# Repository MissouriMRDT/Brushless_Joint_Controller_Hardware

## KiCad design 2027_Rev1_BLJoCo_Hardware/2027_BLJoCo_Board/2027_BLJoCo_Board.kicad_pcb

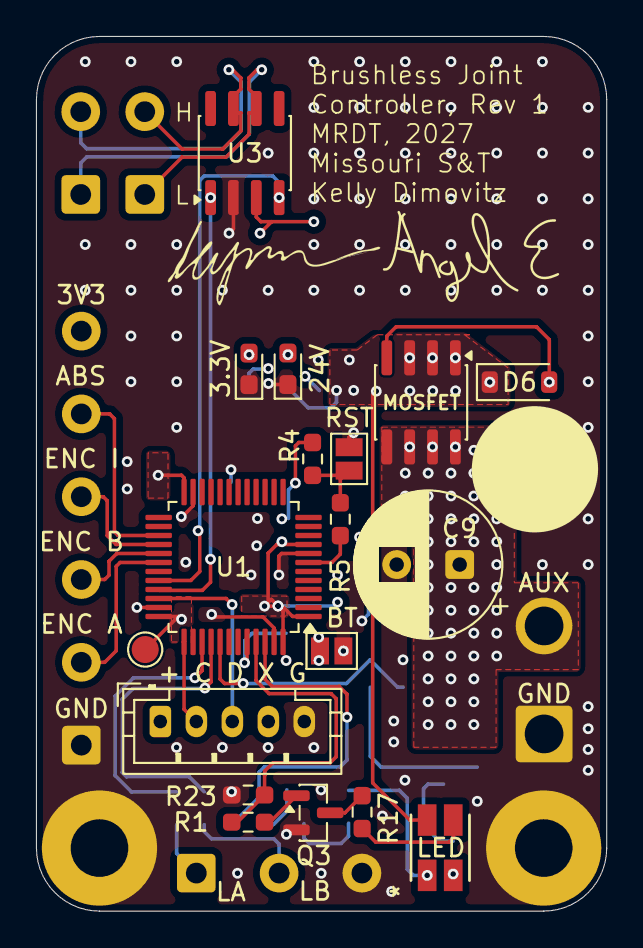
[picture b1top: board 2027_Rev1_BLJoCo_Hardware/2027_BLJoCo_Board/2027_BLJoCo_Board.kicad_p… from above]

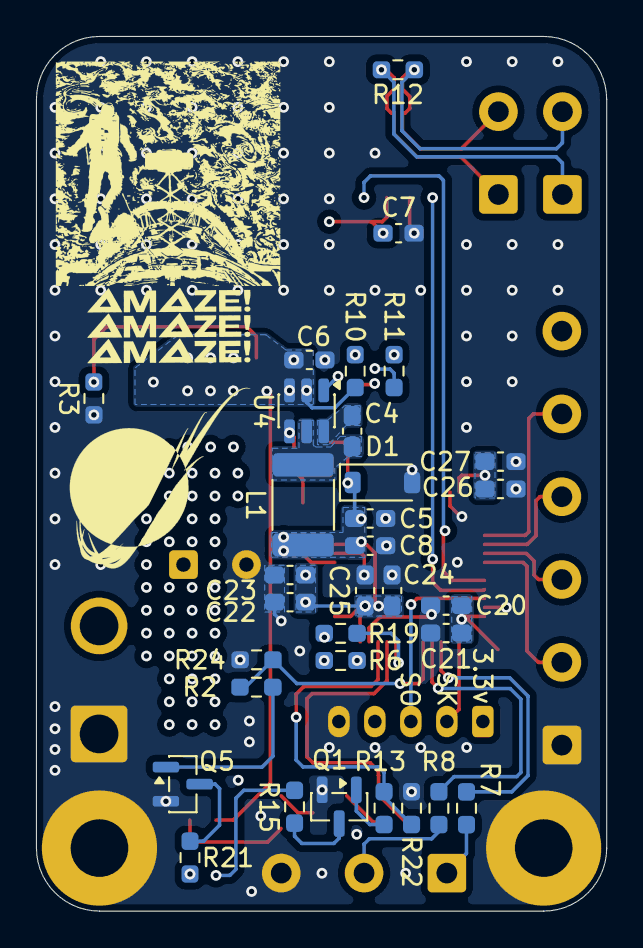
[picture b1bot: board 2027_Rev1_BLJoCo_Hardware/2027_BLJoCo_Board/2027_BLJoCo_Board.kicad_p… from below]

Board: 4 copper layers, 31.7 x 48.6 mm, 57 parts (32 on the bottom side), 39 nets.

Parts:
3.3V, 24V: GREEN; LED_0603_1608Metric_Pad1.05x0.95mm_HandSolder
3.3V#2: TestPoint; TestPoint_Pad_D1.5mm
+ C D X G: Conn_01x05; JST_PH_B5B-PH-K_1x05_P2.00mm_Vertical
AUX: Conn_01x02; SolderWire-1.5sqmm_1x02_P6mm_D1.7mm_OD3mm
BT: Jumper_2_Open; SolderJumper-2_P1.3mm_Open_Pad1.0x1.5mm
C4, C7, C21, C25, C26, C27: 100nF; C_0603_1608Metric_Pad1.08x0.95mm_HandSolder
C5, C8: 22uF; C_0603_1608Metric_Pad1.08x0.95mm_HandSolder
C6: 10uF; C_0603_1608Metric_Pad1.08x0.95mm_HandSolder
C9: 100uf; CP_Radial_D8.0mm_P3.50mm
C20, C24: 4.7uF; C_0603_1608Metric_Pad1.08x0.95mm_HandSolder
C22: 10nF; C_0603_1608Metric_Pad1.08x0.95mm_HandSolder
C23: 1uF; C_0603_1608Metric_Pad1.08x0.95mm_HandSolder
D1: MMSZ4685-TP; D_SOD-123
D6: MMSZ5240BT1G; D_SOD-123
ENC A: Conn_01x06; SolderWire-0.5sqmm_1x06_P4.6mm_D0.9mm_OD2.1mm
H1, H2: MountingHole_Pad; MountingHole_3.2mm_M3_Pad
J6, J8: Conn_01x02; SolderWire-0.5sqmm_1x02_P4.6mm_D0.9mm_OD2.1mm
L1: 3.9uH; L_1812_4532Metric_Pad1.30x3.40mm_HandSolder
LA: Conn_01x03; SolderWire-0.5sqmm_1x03_P4.6mm_D0.9mm_OD2.1mm
LED: XZMDKCBDDG45S-9; PLCC4_3p5x2p8_SLD-M
MOSFET: TPC8132_LQS; SOIC-8_3.9x4.9mm_P1.27mm
Q1, Q3, Q5: BSS138; SOT-23
R1, R2, R7, R8, R13: 100; R_0603_1608Metric_Pad0.98x0.95mm_HandSolder
R3, R22, R23, R24: 1k; R_0603_1608Metric_Pad0.98x0.95mm_HandSolder
R4, R6: 10k; R_0603_1608Metric_Pad0.98x0.95mm_HandSolder
R5, R11, R19: 330; R_0603_1608Metric_Pad0.98x0.95mm_HandSolder
R10: 5.5k; R_0603_1608Metric_Pad0.98x0.95mm_HandSolder
R12: 120; R_0603_1608Metric_Pad0.98x0.95mm_HandSolder
R15, R17: 200; R_0603_1608Metric_Pad0.98x0.95mm_HandSolder
R21: 350; R_0603_1608Metric_Pad0.98x0.95mm_HandSolder
RST: Jumper_2_Open; SolderJumper-2_P1.3mm_Open_Pad1.0x1.5mm
U1: STM32F072C8Tx; LQFP-48_7x7mm_P0.5mm
U3: SN65HVD232; SOIC-8_3.9x4.9mm_P1.27mm
U4: AP63203WU; TSOT-23-6

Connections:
+3.3V: 3.3V#2.1 (1_1), + C D X G.1, C5.1, C7.1, C8.1, C20.1, C21.1, C22.1, C23.1, C24.1, C25.1, C26.1, C27.1, D1.1 (K), ENC A.6, L1.2, R4.1, R6.1, R11.1, U1.1 (VBAT), U1.9 (VDDA), U1.24 (VDD), U1.36 (VDDIO2), U1.48 (VDD), U3.3 (VCC), U4.1 (FB)
+24V: C6.1, D6.1, LED.2, MOSFET.1 (S), MOSFET.2, MOSFET.3, R10.1, U4.2 (EN), U4.3 (IN)
/CAN RX: U1.32 (PA11), U3.4 (R)
/CAN TX: U1.33 (PA12), U3.1 (D)
/CAN+: J6.2, J8.2, R12.1, U3.7 (CANH)
/CAN-: J6.1, J8.1, R12.2, U3.6 (CANL)
/ENC A: ENC A.2, U1.30 (PA9)
/ENC B: ENC A.3, U1.29 (PA8)
/ENC I: ENC A.4, U1.28 (PB15)
/ENC_ABS: ENC A.5, U1.27 (PB14)
/LIM A: LA.1, R7.1
/LIM B: LA.2, R8.1
/SWDCLK: + C D X G.2, U1.37 (PA14)
/SWDIO: + C D X G.3, U1.34 (PA13)
/boot: R19.1, U1.44 (BOOT0)
/nrst: R5.1, U1.7 (NRST)
GND: 3.3V.1 (K), 24V.1 (K), + C D X G.5, AUX.1, BT.2 (B), C5.2, C6.2, C7.2, C8.2, C9.2, C20.2, C21.2, C22.2, C23.2, C24.2, C25.2, C26.2, C27.2, D1.2 (A), ENC A.1, H1.1 (1_1), H2.1 (1_1), LA.3, Q1.2 (S), Q3.2 (S), Q5.2 (S), R3.2, R22.2, R23.2, R24.2, RST.2 (B), U1.8 (VSSA), U1.23 (VSS), U1.35 (VSS), U1.47 (VSS), U3.2 (GND), U4.4 (GND)
LED_B: R13.1, R22.1, U1.46 (PB9)
LED_G: R1.1, R23.1, U1.45 (PB8)
LED_R: R2.1, R24.1, U1.41 (PB5)
unnamed: 24V.2 (A), R10.2
unnamed: 3.3V.2 (A), R11.2
unnamed: R4.2, R5.2, RST.1 (A)
unnamed: BT.1 (A), R6.2, R19.2
unnamed: D6.2, MOSFET.4 (G), R3.1
unnamed: Q1.3 (D), R15.2
unnamed: Q1.1 (G), R13.2
unnamed: Q3.3 (D), R17.2
unnamed: Q3.1 (G), R1.2
unnamed: Q5.3 (D), R21.2
unnamed: Q5.1 (G), R2.2
unnamed: R7.2, U1.39 (PB3)
unnamed: R8.2, U1.40 (PB4)
unnamed: C4.2, U4.6 (BST)
unnamed: C4.1, L1.1, U4.5 (SW)
V_AUX: AUX.2, C9.1, MOSFET.5 (D), MOSFET.6, MOSFET.7, MOSFET.8
led_B_Out: LED.1, R15.1
led_G_Out: LED.3, R17.1
led_R_Out: LED.4, R21.1

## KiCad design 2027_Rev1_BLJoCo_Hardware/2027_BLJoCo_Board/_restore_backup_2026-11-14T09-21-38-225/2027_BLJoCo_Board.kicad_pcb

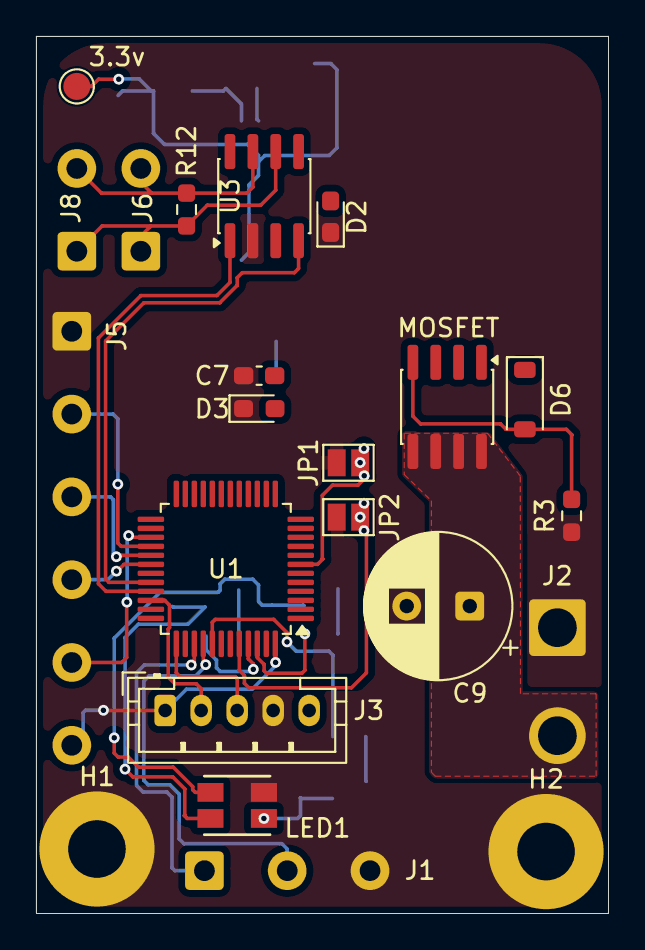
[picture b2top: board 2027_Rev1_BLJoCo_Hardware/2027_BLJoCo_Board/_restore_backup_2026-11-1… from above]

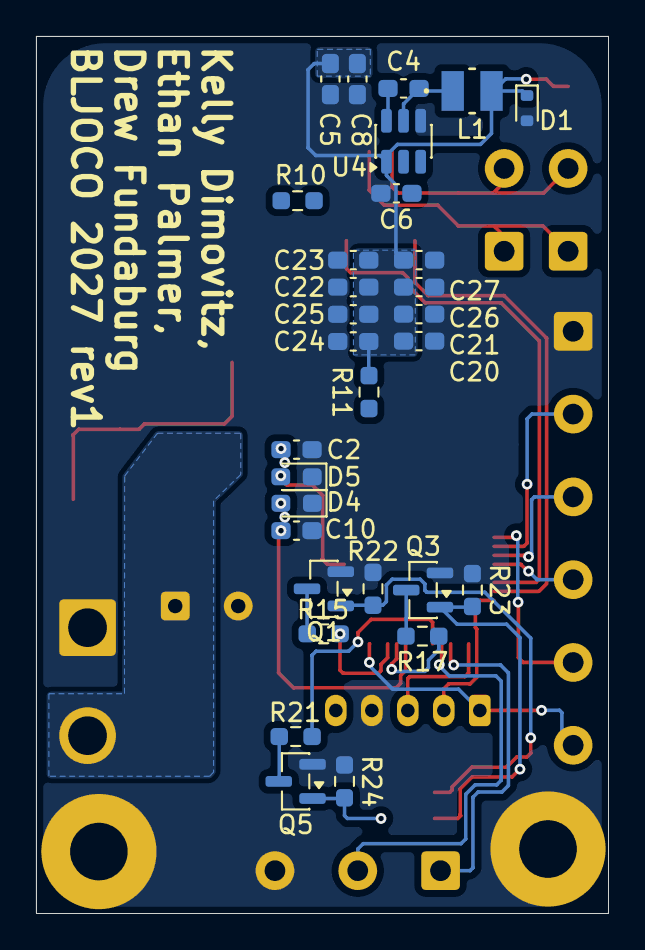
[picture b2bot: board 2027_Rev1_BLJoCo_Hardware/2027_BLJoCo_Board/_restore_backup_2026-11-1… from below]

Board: 2 copper layers, 31.8 x 48.7 mm, 52 parts (30 on the bottom side), 32 nets.

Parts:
3.3v: TestPoint; TestPoint_Pad_D1.5mm
C2, C4, C7, C10, C21, C25, C26, C27: 100nF; C_0603_1608Metric_Pad1.08x0.95mm_HandSolder
C5, C8: 22uF; C_0603_1608Metric_Pad1.08x0.95mm_HandSolder
C6: 10uF; C_0603_1608Metric_Pad1.08x0.95mm_HandSolder
C9: 100uf; CP_Radial_D8.0mm_P3.50mm
C20, C24: 4.7uF; C_0603_1608Metric_Pad1.08x0.95mm_HandSolder
C22: 10nF; C_0603_1608Metric_Pad1.08x0.95mm_HandSolder
C23: 1uF; C_0603_1608Metric_Pad1.08x0.95mm_HandSolder
D1: MMSZ4685-TP; D_SOD-523
D2, D3: GREEN; LED_0603_1608Metric_Pad1.05x0.95mm_HandSolder
D4, D5: D_TVS; D_0603_1608Metric_Pad1.05x0.95mm_HandSolder
D6: MMSZ5240BT1G; D_SOD-123
H1, H2: MountingHole_Pad; MountingHole_3.2mm_M3_Pad
J1: Conn_01x03; SolderWire-0.5sqmm_1x03_P4.6mm_D0.9mm_OD2.1mm
J2: Conn_01x02; SolderWire-1.5sqmm_1x02_P6mm_D1.7mm_OD3mm
J3: Conn_01x05; JST_PH_B5B-PH-K_1x05_P2.00mm_Vertical
J5: Conn_01x06; SolderWire-0.5sqmm_1x06_P4.6mm_D0.9mm_OD2.1mm
J6, J8: Conn_01x02; SolderWire-0.5sqmm_1x02_P4.6mm_D0.9mm_OD2.1mm
JP1, JP2: Jumper_2_Open; SolderJumper-2_P1.3mm_Open_Pad1.0x1.5mm
L1: 3.9uH; IND_TFM252012ALMA1R0MTAA_TDK
LED1: XZM2CRKM2DGFBB45SCCB; PLCC4_3p5x2p8_SLD
MOSFET: TPC8132_LQS; SOIC-8_3.9x4.9mm_P1.27mm
Q1, Q3, Q5: BSS138; SOT-23
R3, R22, R23, R24: 1k; R_0603_1608Metric_Pad0.98x0.95mm_HandSolder
R10: 5.5k; R_0603_1608Metric_Pad0.98x0.95mm_HandSolder
R11: 330; R_0603_1608Metric_Pad0.98x0.95mm_HandSolder
R12: 120; R_0603_1608Metric_Pad0.98x0.95mm_HandSolder
R15, R17: 200; R_0603_1608Metric_Pad0.98x0.95mm_HandSolder
R21: 350; R_0603_1608Metric_Pad0.98x0.95mm_HandSolder
U1: STM32F072C8Tx; LQFP-48_7x7mm_P0.5mm
U3: SN65HVD232; SOIC-8_3.9x4.9mm_P1.27mm
U4: AP63203WU; TSOT-23-6

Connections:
+3.3V: 3.3v.1 (1_1), C5.1, C7.1, C8.1, C20.1, C21.1, C22.1, C23.1, C24.1, C25.1, C26.1, C27.1, D1.1 (K), J3.1, J5.6, L1.2, R11.1, U1.1 (VBAT), U1.9 (VDDA), U1.24 (VDD), U1.48 (VDD), U3.3 (VCC), U4.1 (FB)
+24V: C6.1, D6.1, MOSFET.1 (S), MOSFET.2, MOSFET.3, R10.1, U4.2 (EN), U4.3 (IN)
/CAN RX: U1.32 (PA11), U3.4 (R)
/CAN TX: U1.33 (PA12), U3.1 (D)
/CANH: J6.2, J8.2, R12.1, U3.7 (CANH)
/CANL: J6.1, J8.1, R12.2, U3.6 (CANL)
/ENC A: J5.4, U1.30 (PA9)
/ENC B: J5.3, U1.29 (PA8)
/ENC I: J5.2, U1.28 (PB15)
/ENC_ABS: J5.5, U1.27 (PB14)
/LIM A: J1.1, U1.39 (PB3)
/LIM B: J1.2, U1.40 (PB4)
/SWDCLK: J3.2, U1.34 (PA13)
/SWDIO: J3.3, U1.37 (PA14)
/boot: C10.1, D4.2 (A2), JP2.2 (B), U1.44 (BOOT0)
/nrst: C2.1, D5.2 (A2), JP1.2 (B), U1.7 (NRST)
GND: C2.2, C5.2, C6.2, C7.2, C8.2, C9.2, C10.2, C20.2, C21.2, C22.2, C23.2, C24.2, C25.2, C26.2, C27.2, D1.2 (A), D2.1 (K), D3.1 (K), D4.1 (A1), D5.1 (A1), H1.1 (1_1), H2.1 (1_1), J1.3, J2.1, J3.4, J5.1, JP1.1 (A), JP2.1 (A), LED1.4, Q1.2 (S), Q3.2 (S), Q5.2 (S), R3.2, R22.2, R23.2, R24.2, U1.8 (VSSA), U1.23 (VSS), U1.35 (VSS), U1.47 (VSS), U3.2 (GND), U4.4 (GND)
LED_B: R15.1, U1.46 (PB9)
LED_G: R17.1, U1.45 (PB8)
LED_R: R21.1, U1.41 (PB5)
unnamed: D2.2 (A), R10.2
unnamed: D3.2 (A), R11.2
unnamed: D6.2, MOSFET.4 (G), R3.1
unnamed: Q1.3 (D), R15.2
unnamed: Q3.3 (D), R17.2
unnamed: Q5.3 (D), R21.2
unnamed: C4.2, U4.6 (BST)
unnamed: C4.1, L1.1, U4.5 (SW)
V_AUX: C9.1, J2.2, MOSFET.5 (D), MOSFET.6, MOSFET.7, MOSFET.8
led_B_Out: LED1.3, Q1.1 (G), R22.1
led_G_Out: LED1.2, Q3.1 (G), R23.1
led_R_Out: LED1.1, Q5.1 (G), R24.1
